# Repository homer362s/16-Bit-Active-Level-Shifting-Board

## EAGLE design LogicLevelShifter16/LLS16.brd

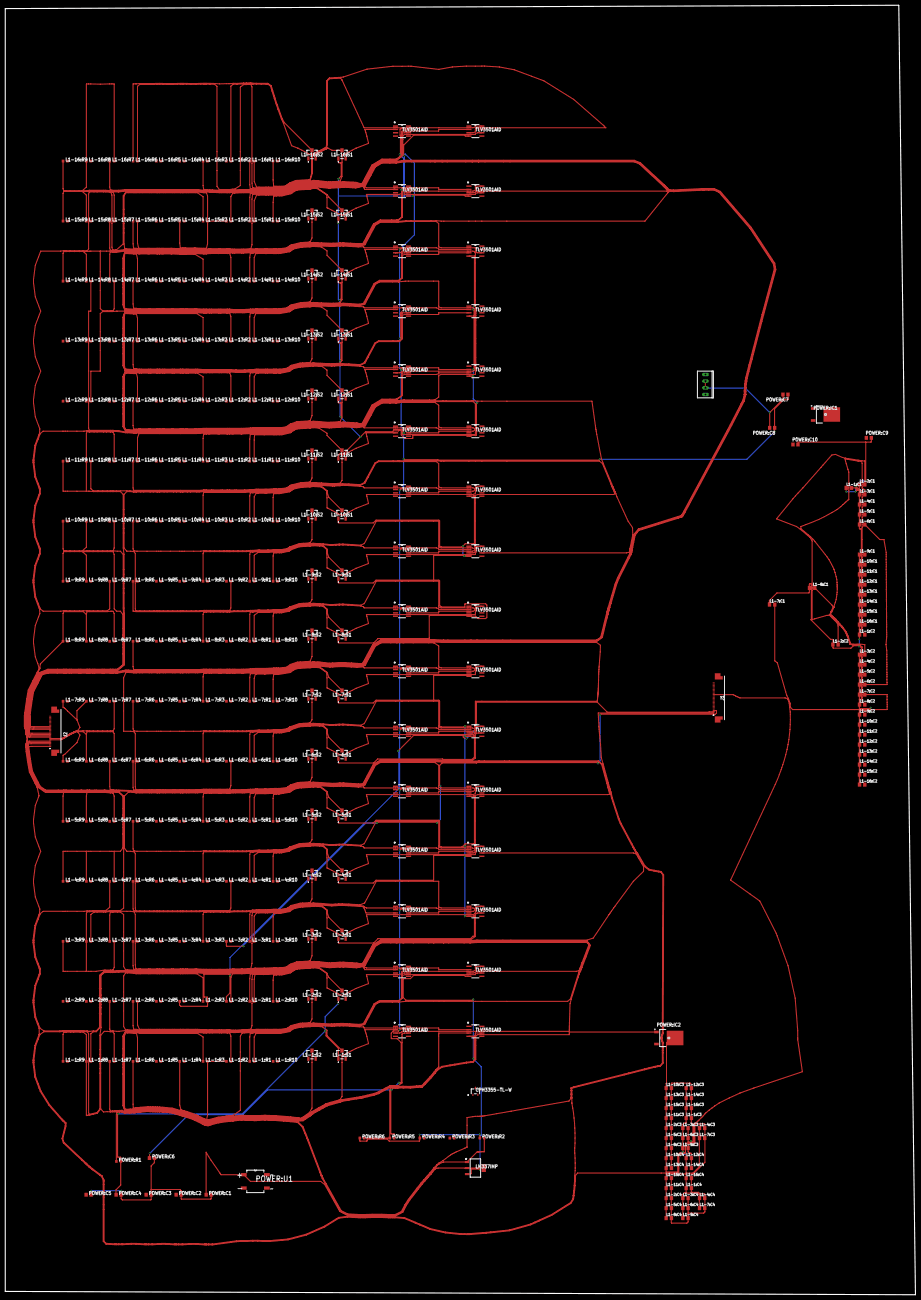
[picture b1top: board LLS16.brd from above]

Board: 2 copper layers, 346.7 x 491.2 mm, 312 parts (0 on the bottom side), 220 nets.

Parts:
J1, J2: 0524372471
L1-1:C1, L1-1:C2, L1-1:C3, L1-1:C4, L1-2:C1, L1-2:C2, L1-2:C3, L1-2:C4, L1-3:C1, L1-3:C2, L1-3:C3, L1-3:C4, L1-4:C1, L1-4:C2, L1-4:C3, L1-4:C4, L1-5:C1, L1-5:C2, L1-5:C3, L1-5:C4, L1-6:C1, L1-6:C2, L1-6:C3, L1-6:C4, L1-7:C1, L1-7:C2, L1-7:C3, L1-7:C4, L1-8:C1, L1-8:C2, L1-8:C3, L1-8:C4, L1-9:C1, L1-9:C2, L1-9:C3, L1-9:C4, L1-10:C1, L1-10:C2, L1-10:C3, L1-10:C4, L1-11:C1, L1-11:C2, L1-11:C3, L1-11:C4, L1-12:C1, L1-12:C2, L1-12:C3, L1-12:C4, L1-13:C1, L1-13:C2, L1-13:C3, L1-13:C4, L1-14:C1, L1-14:C2, L1-14:C3, L1-14:C4, L1-15:C1, L1-15:C2, L1-15:C3, L1-15:C4, L1-16:C1, L1-16:C2, L1-16:C3, L1-16:C4: C0805K
L1-1:R1, L1-1:R2, L1-1:R6, L1-1:R8, L1-2:R1, L1-2:R2, L1-2:R6, L1-2:R8, L1-3:R1, L1-3:R2, L1-3:R6, L1-3:R8, L1-4:R1, L1-4:R2, L1-4:R6, L1-4:R8, L1-5:R1, L1-5:R2, L1-5:R6, L1-5:R8, L1-6:R1, L1-6:R2, L1-6:R6, L1-6:R8, L1-7:R1, L1-7:R2, L1-7:R6, L1-7:R8, L1-8:R1, L1-8:R2, L1-8:R6, L1-8:R8, L1-9:R1, L1-9:R2, L1-9:R6, L1-9:R8, L1-10:R1, L1-10:R2, L1-10:R6, L1-10:R8, L1-11:R1, L1-11:R2, L1-11:R6, L1-11:R8, L1-12:R1, L1-12:R2, L1-12:R6, L1-12:R8, L1-13:R1, L1-13:R2, L1-13:R6, L1-13:R8, L1-14:R1, L1-14:R2, L1-14:R6, L1-14:R8, L1-15:R1, L1-15:R2, L1-15:R6, L1-15:R8, L1-16:R1, L1-16:R2, L1-16:R6, L1-16:R8: 130; R0603
L1-1:R3, L1-1:R4, L1-1:R7, L1-1:R9, L1-1:R10, L1-2:R3, L1-2:R4, L1-2:R7, L1-2:R9, L1-2:R10, L1-3:R3, L1-3:R4, L1-3:R7, L1-3:R9, L1-3:R10, L1-4:R3, L1-4:R4, L1-4:R7, L1-4:R9, L1-4:R10, L1-5:R3, L1-5:R4, L1-5:R7, L1-5:R9, L1-5:R10, L1-6:R3, L1-6:R4, L1-6:R7, L1-6:R9, L1-6:R10, L1-7:R3, L1-7:R4, L1-7:R7, L1-7:R9, L1-7:R10, L1-8:R3, L1-8:R4, L1-8:R7, L1-8:R9, L1-8:R10, L1-9:R3, L1-9:R4, L1-9:R7, L1-9:R9, L1-9:R10, L1-10:R3, L1-10:R4, L1-10:R7, L1-10:R9, L1-10:R10, L1-11:R3, L1-11:R4, L1-11:R7, L1-11:R9, L1-11:R10, L1-12:R3, L1-12:R4, L1-12:R7, L1-12:R9, L1-12:R10, L1-13:R3, L1-13:R4, L1-13:R7, L1-13:R9, L1-13:R10, L1-14:R3, L1-14:R4, L1-14:R7, L1-14:R9, L1-14:R10, L1-15:R3, L1-15:R4, L1-15:R7, L1-15:R9, L1-15:R10, L1-16:R3, L1-16:R4, L1-16:R7, L1-16:R9, L1-16:R10: 220; R0603
L1-1:R5, L1-2:R5, L1-3:R5, L1-4:R5, L1-5:R5, L1-6:R5, L1-7:R5, L1-8:R5, L1-9:R5, L1-10:R5, L1-11:R5, L1-12:R5, L1-13:R5, L1-14:R5, L1-15:R5, L1-16:R5: 51; R0603
L1-1:S1, L1-1:S2, L1-2:S1, L1-2:S2, L1-3:S1, L1-3:S2, L1-4:S1, L1-4:S2, L1-5:S1, L1-5:S2, L1-6:S1, L1-6:S2, L1-7:S1, L1-7:S2, L1-8:S1, L1-8:S2, L1-9:S1, L1-9:S2, L1-10:S1, L1-10:S2, L1-11:S1, L1-11:S2, L1-12:S1, L1-12:S2, L1-13:S1, L1-13:S2, L1-14:S1, L1-14:S2, L1-15:S1, L1-15:S2, L1-16:S1, L1-16:S2: SM-3TW102; SM3TW102
L1-1:U1, L1-1:U2, L1-2:U1, L1-2:U2, L1-3:U1, L1-3:U2, L1-4:U1, L1-4:U2, L1-5:U1, L1-5:U2, L1-6:U1, L1-6:U2, L1-7:U1, L1-7:U2, L1-8:U1, L1-8:U2, L1-9:U1, L1-9:U2, L1-10:U1, L1-10:U2, L1-11:U1, L1-11:U2, L1-12:U1, L1-12:U2, L1-13:U1, L1-13:U2, L1-14:U1, L1-14:U2, L1-15:U1, L1-15:U2, L1-16:U1, L1-16:U2: TLV3501AID; D8
POWER:C1, POWER:C2, POWER:C3: 10uF; C0805
POWER:C4, POWER:C5, POWER:C6: 0.1uF; C0805
POWER:C7, POWER:C9: 0.1 uF; C0805
POWER:C8, POWER:C10: 2.2 uF; C0805
POWER:IC1, POWER:IC2: LM317AMDT_NOPB; TO228P991X238-3N
POWER:R1, POWER:R3, POWER:R5: 240; R0603
POWER:R2, POWER:R4, POWER:R6: 49.9; R0603
POWER:U1: DF10S; SOT508P985X260-4N
POWER:U2: LM337IMP; MP04A_TEX
U1: CPH3355-TL-W; CPH3_2P9X1P6_ONS
U$1: CONNHEADERVERT4POS2.54MM

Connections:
+1.5V: L1-1:S1.3, L1-1:S2.1, L1-1:U1.7, L1-2:S1.3, L1-2:S2.1, L1-2:U1.7, L1-3:S1.3, L1-3:S2.1, L1-3:U1.7, L1-4:S1.3, L1-4:S2.1, L1-4:U1.7, L1-5:S1.3, L1-5:S2.1, L1-5:U1.7, L1-6:S1.3, L1-6:S2.1, L1-6:U1.7, L1-7:S1.3, L1-7:S2.1, L1-7:U1.7, L1-8:S1.3, L1-8:S2.1, L1-8:U1.7, L1-9:S1.3, L1-9:S2.1, L1-9:U1.7, L1-10:S1.3, L1-10:S2.1, L1-10:U1.7, L1-11:S1.3, L1-11:S2.1, L1-11:U1.7, L1-12:S1.3, L1-12:S2.1, L1-12:U1.7, L1-13:S1.3, L1-13:S2.1, L1-13:U1.7, L1-14:S1.3, L1-14:S2.1, L1-14:U1.7, L1-15:S1.3, L1-15:S2.1, L1-15:U1.7, L1-16:S1.3, L1-16:S2.1, L1-16:U1.7, POWER:C5.1, POWER:C9.1, POWER:C10.1, POWER:IC1.4, POWER:R3.2, U1.2
+3V: L1-1:C3.1, L1-1:C4.1, L1-1:U2.7, L1-2:C3.1, L1-2:C4.1, L1-2:U2.7, L1-3:C3.1, L1-3:C4.1, L1-3:U2.7, L1-4:C3.1, L1-4:C4.1, L1-4:U2.7, L1-5:C3.1, L1-5:C4.1, L1-5:U2.7, L1-6:C3.1, L1-6:C4.1, L1-6:U2.7, L1-7:C3.1, L1-7:C4.1, L1-7:U2.7, L1-8:C3.1, L1-8:C4.1, L1-8:U2.7, L1-9:C3.1, L1-9:C4.1, L1-9:U2.7, L1-10:C3.1, L1-10:C4.1, L1-10:U2.7, L1-11:C3.1, L1-11:C4.1, L1-11:U2.7, L1-12:C3.1, L1-12:C4.1, L1-12:U2.7, L1-13:C3.1, L1-13:C4.1, L1-13:U2.7, L1-14:C3.1, L1-14:C4.1, L1-14:U2.7, L1-15:C3.1, L1-15:C4.1, L1-15:U2.7, L1-16:C3.1, L1-16:C4.1, L1-16:U2.7, POWER:C6.1, POWER:C7.1, POWER:C8.1, POWER:IC2.4, POWER:R5.2
+5V: POWER:U1.4, U$1.4
-1.5V: L1-1:C1.1, L1-1:C2.1, L1-1:S1.1, L1-1:U1.4, L1-2:C1.1, L1-2:C2.1, L1-2:S1.1, L1-2:U1.4, L1-3:C1.1, L1-3:C2.1, L1-3:S1.1, L1-3:U1.4, L1-4:C1.1, L1-4:C2.1, L1-4:S1.1, L1-4:U1.4, L1-5:C1.1, L1-5:C2.1, L1-5:S1.1, L1-5:U1.4, L1-6:C1.1, L1-6:C2.1, L1-6:S1.1, L1-6:U1.4, L1-7:C1.1, L1-7:C2.1, L1-7:S1.1, L1-7:U1.4, L1-8:C1.1, L1-8:C2.1, L1-8:S1.1, L1-8:U1.4, L1-9:C1.1, L1-9:C2.1, L1-9:S1.1, L1-9:U1.4, L1-10:C1.1, L1-10:C2.1, L1-10:S1.1, L1-10:U1.4, L1-11:C1.1, L1-11:C2.1, L1-11:S1.1, L1-11:U1.4, L1-12:C1.1, L1-12:C2.1, L1-12:S1.1, L1-12:U1.4, L1-13:C1.1, L1-13:C2.1, L1-13:S1.1, L1-13:U1.4, L1-14:C1.1, L1-14:C2.1, L1-14:S1.1, L1-14:U1.4, L1-15:C1.1, L1-15:C2.1, L1-15:S1.1, L1-15:U1.4, L1-16:C1.1, L1-16:C2.1, L1-16:S1.1, L1-16:U1.4, POWER:C4.1, POWER:C9.2, POWER:C10.2, POWER:R1.2, POWER:U2.3
D: L1-1:R5.1, L1-1:U2.8, L1-2:R5.1, L1-2:U2.8, L1-3:R5.1, L1-3:U2.8, L1-4:R5.1, L1-4:U2.8, L1-5:R5.1, L1-5:U2.8, L1-6:R5.1, L1-6:U2.8, L1-7:R5.1, L1-7:U2.8, L1-8:R5.1, L1-8:U2.8, L1-9:R5.1, L1-9:U2.8, L1-10:R5.1, L1-10:U2.8, L1-11:R5.1, L1-11:U2.8, L1-12:R5.1, L1-12:U2.8, L1-13:R5.1, L1-13:U2.8, L1-14:R5.1, L1-14:U2.8, L1-15:R5.1, L1-15:U2.8, L1-16:R5.1, L1-16:U2.8, U1.3
F1: J1.1, L1-1:R2.1, L1-1:R3.2, L1-1:R4.1
F2: J1.2, L1-2:R2.1, L1-2:R3.2, L1-2:R4.1
F3: J1.3, L1-3:R2.1, L1-3:R3.2, L1-3:R4.1
F4: J1.4, L1-4:R2.1, L1-4:R3.2, L1-4:R4.1
F5: J1.5, L1-5:R2.1, L1-5:R3.2, L1-5:R4.1
F6: J1.6, L1-6:R2.1, L1-6:R3.2, L1-6:R4.1
F7: J1.7, L1-7:R2.1, L1-7:R3.2, L1-7:R4.1
F8: J1.8, L1-8:R2.1, L1-8:R3.2, L1-8:R4.1
F9: J1.9, L1-9:R2.1, L1-9:R3.2, L1-9:R4.1
F10: J1.10, L1-10:R2.1, L1-10:R3.2, L1-10:R4.1
F11: J1.11, L1-11:R2.1, L1-11:R3.2, L1-11:R4.1
F12: J1.12, L1-12:R2.1, L1-12:R3.2, L1-12:R4.1
F13: J1.13, L1-13:R2.1, L1-13:R3.2, L1-13:R4.1
F14: J1.14, L1-14:R2.1, L1-14:R3.2, L1-14:R4.1
F15: J1.15, L1-15:R2.1, L1-15:R3.2, L1-15:R4.1
F16: J1.16, L1-16:R2.1, L1-16:R3.2, L1-16:R4.1
G: L1-1:R10.2, L1-2:R10.2, L1-3:R10.2, L1-4:R10.2, L1-5:R10.2, L1-6:R10.2, L1-7:R10.2, L1-8:R10.2, L1-9:R10.2, L1-10:R10.2, L1-11:R10.2, L1-12:R10.2, L1-13:R10.2, L1-14:R10.2, L1-15:R10.2, L1-16:R10.2, U1.1
GND: L1-1:C3.2, L1-1:C4.2, L1-2:C3.2, L1-2:C4.2, L1-3:C3.2, L1-3:C4.2, L1-4:C3.2, L1-4:C4.2, L1-5:C3.2, L1-5:C4.2, L1-6:C3.2, L1-6:C4.2, L1-7:C3.2, L1-7:C4.2, L1-8:C3.2, L1-8:C4.2, L1-9:C3.2, L1-9:C4.2, L1-10:C3.2, L1-10:C4.2, L1-11:C3.2, L1-11:C4.2, L1-12:C3.2, L1-12:C4.2, L1-13:C3.2, L1-13:C4.2, L1-14:C3.2, L1-14:C4.2, L1-15:C3.2, L1-15:C4.2, L1-16:C3.2, L1-16:C4.2, POWER:C1.2, POWER:C2.2, POWER:C3.2, POWER:C4.2, POWER:C5.2, POWER:C6.2, POWER:C7.2, POWER:C8.2, POWER:R2.1, POWER:R4.1, POWER:R6.1, U$1.2, U$1.3
L1-1:+1.5: L1-1:C1.2, L1-1:C2.2
L1-1:GND!: L1-1:R4.2, L1-1:R5.2, L1-1:R9.2, L1-1:S2.3, L1-1:U2.4
L1-1:N$1: L1-1:R1.2, L1-1:S1.2
L1-1:N$2: L1-1:R1.1, L1-1:U1.2
L1-1:N$3: L1-1:R2.2, L1-1:U1.3
L1-1:N$5: L1-1:R3.1, L1-1:U2.6
L1-1:N$6: L1-1:R6.1, L1-1:S2.2
L1-1:N$7: L1-1:R6.2, L1-1:U2.2
L1-1:N$8: L1-1:R8.2, L1-1:U2.3
L1-1:N$10: L1-1:R7.1, L1-1:U1.6
L1-1:N$11: L1-1:R10.1, L1-1:U1.8
L1-2:+1.5: L1-2:C1.2, L1-2:C2.2
L1-2:GND!: L1-2:R4.2, L1-2:R5.2, L1-2:R9.2, L1-2:S2.3, L1-2:U2.4
L1-2:N$1: L1-2:R1.2, L1-2:S1.2
L1-2:N$2: L1-2:R1.1, L1-2:U1.2
L1-2:N$3: L1-2:R2.2, L1-2:U1.3
L1-2:N$5: L1-2:R3.1, L1-2:U2.6
L1-2:N$6: L1-2:R6.1, L1-2:S2.2
L1-2:N$7: L1-2:R6.2, L1-2:U2.2
L1-2:N$8: L1-2:R8.2, L1-2:U2.3
L1-2:N$10: L1-2:R7.1, L1-2:U1.6
L1-2:N$11: L1-2:R10.1, L1-2:U1.8
L1-3:+1.5: L1-3:C1.2, L1-3:C2.2
L1-3:GND!: L1-3:R4.2, L1-3:R5.2, L1-3:R9.2, L1-3:S2.3, L1-3:U2.4
L1-3:N$1: L1-3:R1.2, L1-3:S1.2
L1-3:N$2: L1-3:R1.1, L1-3:U1.2
L1-3:N$3: L1-3:R2.2, L1-3:U1.3
L1-3:N$5: L1-3:R3.1, L1-3:U2.6
L1-3:N$6: L1-3:R6.1, L1-3:S2.2
L1-3:N$7: L1-3:R6.2, L1-3:U2.2
L1-3:N$8: L1-3:R8.2, L1-3:U2.3
L1-3:N$10: L1-3:R7.1, L1-3:U1.6
L1-3:N$11: L1-3:R10.1, L1-3:U1.8
L1-4:+1.5: L1-4:C1.2, L1-4:C2.2
L1-4:GND!: L1-4:R4.2, L1-4:R5.2, L1-4:R9.2, L1-4:S2.3, L1-4:U2.4
L1-4:N$1: L1-4:R1.2, L1-4:S1.2
L1-4:N$2: L1-4:R1.1, L1-4:U1.2
L1-4:N$3: L1-4:R2.2, L1-4:U1.3
L1-4:N$5: L1-4:R3.1, L1-4:U2.6
L1-4:N$6: L1-4:R6.1, L1-4:S2.2
L1-4:N$7: L1-4:R6.2, L1-4:U2.2
L1-4:N$8: L1-4:R8.2, L1-4:U2.3
L1-4:N$10: L1-4:R7.1, L1-4:U1.6
L1-4:N$11: L1-4:R10.1, L1-4:U1.8
L1-5:+1.5: L1-5:C1.2, L1-5:C2.2
L1-5:GND!: L1-5:R4.2, L1-5:R5.2, L1-5:R9.2, L1-5:S2.3, L1-5:U2.4
L1-5:N$1: L1-5:R1.2, L1-5:S1.2
L1-5:N$2: L1-5:R1.1, L1-5:U1.2
L1-5:N$3: L1-5:R2.2, L1-5:U1.3
L1-5:N$5: L1-5:R3.1, L1-5:U2.6
L1-5:N$6: L1-5:R6.1, L1-5:S2.2
L1-5:N$7: L1-5:R6.2, L1-5:U2.2
L1-5:N$8: L1-5:R8.2, L1-5:U2.3
L1-5:N$10: L1-5:R7.1, L1-5:U1.6
L1-5:N$11: L1-5:R10.1, L1-5:U1.8
L1-6:+1.5: L1-6:C1.2, L1-6:C2.2
L1-6:GND!: L1-6:R4.2, L1-6:R5.2, L1-6:R9.2, L1-6:S2.3, L1-6:U2.4
L1-6:N$1: L1-6:R1.2, L1-6:S1.2
L1-6:N$2: L1-6:R1.1, L1-6:U1.2
L1-6:N$3: L1-6:R2.2, L1-6:U1.3
L1-6:N$5: L1-6:R3.1, L1-6:U2.6
L1-6:N$6: L1-6:R6.1, L1-6:S2.2
L1-6:N$7: L1-6:R6.2, L1-6:U2.2
L1-6:N$8: L1-6:R8.2, L1-6:U2.3
L1-6:N$10: L1-6:R7.1, L1-6:U1.6
L1-6:N$11: L1-6:R10.1, L1-6:U1.8
L1-7:+1.5: L1-7:C1.2, L1-7:C2.2
L1-7:GND!: L1-7:R4.2, L1-7:R5.2, L1-7:R9.2, L1-7:S2.3, L1-7:U2.4
L1-7:N$1: L1-7:R1.2, L1-7:S1.2
L1-7:N$2: L1-7:R1.1, L1-7:U1.2
L1-7:N$3: L1-7:R2.2, L1-7:U1.3
L1-7:N$5: L1-7:R3.1, L1-7:U2.6
L1-7:N$6: L1-7:R6.1, L1-7:S2.2
L1-7:N$7: L1-7:R6.2, L1-7:U2.2
L1-7:N$8: L1-7:R8.2, L1-7:U2.3
L1-7:N$10: L1-7:R7.1, L1-7:U1.6
L1-7:N$11: L1-7:R10.1, L1-7:U1.8
L1-8:+1.5: L1-8:C1.2, L1-8:C2.2
L1-8:GND!: L1-8:R4.2, L1-8:R5.2, L1-8:R9.2, L1-8:S2.3, L1-8:U2.4
L1-8:N$1: L1-8:R1.2, L1-8:S1.2
L1-8:N$2: L1-8:R1.1, L1-8:U1.2
L1-8:N$3: L1-8:R2.2, L1-8:U1.3
L1-8:N$5: L1-8:R3.1, L1-8:U2.6
L1-8:N$6: L1-8:R6.1, L1-8:S2.2
L1-8:N$7: L1-8:R6.2, L1-8:U2.2
L1-8:N$8: L1-8:R8.2, L1-8:U2.3
L1-8:N$10: L1-8:R7.1, L1-8:U1.6
L1-8:N$11: L1-8:R10.1, L1-8:U1.8
L1-9:+1.5: L1-9:C1.2, L1-9:C2.2
L1-9:GND!: L1-9:R4.2, L1-9:R5.2, L1-9:R9.2, L1-9:S2.3, L1-9:U2.4
L1-9:N$1: L1-9:R1.2, L1-9:S1.2
L1-9:N$2: L1-9:R1.1, L1-9:U1.2
L1-9:N$3: L1-9:R2.2, L1-9:U1.3
L1-9:N$5: L1-9:R3.1, L1-9:U2.6
L1-9:N$6: L1-9:R6.1, L1-9:S2.2
L1-9:N$7: L1-9:R6.2, L1-9:U2.2
L1-9:N$8: L1-9:R8.2, L1-9:U2.3
L1-9:N$10: L1-9:R7.1, L1-9:U1.6
L1-9:N$11: L1-9:R10.1, L1-9:U1.8
L1-10:+1.5: L1-10:C1.2, L1-10:C2.2
L1-10:GND!: L1-10:R4.2, L1-10:R5.2, L1-10:R9.2, L1-10:S2.3, L1-10:U2.4
L1-10:N$1: L1-10:R1.2, L1-10:S1.2
L1-10:N$2: L1-10:R1.1, L1-10:U1.2
L1-10:N$3: L1-10:R2.2, L1-10:U1.3
L1-10:N$5: L1-10:R3.1, L1-10:U2.6
L1-10:N$6: L1-10:R6.1, L1-10:S2.2
L1-10:N$7: L1-10:R6.2, L1-10:U2.2
L1-10:N$8: L1-10:R8.2, L1-10:U2.3
L1-10:N$10: L1-10:R7.1, L1-10:U1.6
L1-10:N$11: L1-10:R10.1, L1-10:U1.8
L1-11:+1.5: L1-11:C1.2, L1-11:C2.2
L1-11:GND!: L1-11:R4.2, L1-11:R5.2, L1-11:R9.2, L1-11:S2.3, L1-11:U2.4
L1-11:N$1: L1-11:R1.2, L1-11:S1.2
L1-11:N$2: L1-11:R1.1, L1-11:U1.2
L1-11:N$3: L1-11:R2.2, L1-11:U1.3
L1-11:N$5: L1-11:R3.1, L1-11:U2.6
L1-11:N$6: L1-11:R6.1, L1-11:S2.2
L1-11:N$7: L1-11:R6.2, L1-11:U2.2
L1-11:N$8: L1-11:R8.2, L1-11:U2.3
L1-11:N$10: L1-11:R7.1, L1-11:U1.6
L1-11:N$11: L1-11:R10.1, L1-11:U1.8
L1-12:+1.5: L1-12:C1.2, L1-12:C2.2
L1-12:GND!: L1-12:R4.2, L1-12:R5.2, L1-12:R9.2, L1-12:S2.3, L1-12:U2.4
L1-12:N$1: L1-12:R1.2, L1-12:S1.2
L1-12:N$2: L1-12:R1.1, L1-12:U1.2
L1-12:N$3: L1-12:R2.2, L1-12:U1.3
L1-12:N$5: L1-12:R3.1, L1-12:U2.6
L1-12:N$6: L1-12:R6.1, L1-12:S2.2
L1-12:N$7: L1-12:R6.2, L1-12:U2.2
L1-12:N$8: L1-12:R8.2, L1-12:U2.3
L1-12:N$10: L1-12:R7.1, L1-12:U1.6
L1-12:N$11: L1-12:R10.1, L1-12:U1.8
L1-13:+1.5: L1-13:C1.2, L1-13:C2.2
L1-13:GND!: L1-13:R4.2, L1-13:R5.2, L1-13:R9.2, L1-13:S2.3, L1-13:U2.4
L1-13:N$1: L1-13:R1.2, L1-13:S1.2
L1-13:N$2: L1-13:R1.1, L1-13:U1.2
L1-13:N$3: L1-13:R2.2, L1-13:U1.3
L1-13:N$5: L1-13:R3.1, L1-13:U2.6
L1-13:N$6: L1-13:R6.1, L1-13:S2.2
L1-13:N$7: L1-13:R6.2, L1-13:U2.2
L1-13:N$8: L1-13:R8.2, L1-13:U2.3
L1-13:N$10: L1-13:R7.1, L1-13:U1.6
L1-13:N$11: L1-13:R10.1, L1-13:U1.8
L1-14:+1.5: L1-14:C1.2, L1-14:C2.2
L1-14:GND!: L1-14:R4.2, L1-14:R5.2, L1-14:R9.2, L1-14:S2.3, L1-14:U2.4
L1-14:N$1: L1-14:R1.2, L1-14:S1.2
L1-14:N$2: L1-14:R1.1, L1-14:U1.2
L1-14:N$3: L1-14:R2.2, L1-14:U1.3
L1-14:N$5: L1-14:R3.1, L1-14:U2.6
L1-14:N$6: L1-14:R6.1, L1-14:S2.2
L1-14:N$7: L1-14:R6.2, L1-14:U2.2
L1-14:N$8: L1-14:R8.2, L1-14:U2.3
L1-14:N$10: L1-14:R7.1, L1-14:U1.6
L1-14:N$11: L1-14:R10.1, L1-14:U1.8
L1-15:+1.5: L1-15:C1.2, L1-15:C2.2
L1-15:GND!: L1-15:R4.2, L1-15:R5.2, L1-15:R9.2, L1-15:S2.3, L1-15:U2.4
L1-15:N$1: L1-15:R1.2, L1-15:S1.2
L1-15:N$2: L1-15:R1.1, L1-15:U1.2
L1-15:N$3: L1-15:R2.2, L1-15:U1.3
L1-15:N$5: L1-15:R3.1, L1-15:U2.6
L1-15:N$6: L1-15:R6.1, L1-15:S2.2
L1-15:N$7: L1-15:R6.2, L1-15:U2.2
L1-15:N$8: L1-15:R8.2, L1-15:U2.3
L1-15:N$10: L1-15:R7.1, L1-15:U1.6
L1-15:N$11: L1-15:R10.1, L1-15:U1.8
L1-16:+1.5: L1-16:C1.2, L1-16:C2.2
L1-16:GND!: L1-16:R4.2, L1-16:R5.2, L1-16:R9.2, L1-16:S2.3, L1-16:U2.4
L1-16:N$1: L1-16:R1.2, L1-16:S1.2
L1-16:N$2: L1-16:R1.1, L1-16:U1.2
L1-16:N$3: L1-16:R2.2, L1-16:U1.3
L1-16:N$5: L1-16:R3.1, L1-16:U2.6
L1-16:N$6: L1-16:R6.1, L1-16:S2.2
L1-16:N$7: L1-16:R6.2, L1-16:U2.2
L1-16:N$8: L1-16:R8.2, L1-16:U2.3
L1-16:N$10: L1-16:R7.1, L1-16:U1.6
L1-16:N$11: L1-16:R10.1, L1-16:U1.8
M1: J2.1, L1-1:R7.2, L1-1:R8.1, L1-1:R9.1
M2: J2.2, L1-2:R7.2, L1-2:R8.1, L1-2:R9.1
M3: J2.3, L1-3:R7.2, L1-3:R8.1, L1-3:R9.1
M4: J2.4, L1-4:R7.2, L1-4:R8.1, L1-4:R9.1
M5: J2.5, L1-5:R7.2, L1-5:R8.1, L1-5:R9.1
M6: J2.6, L1-6:R7.2, L1-6:R8.1, L1-6:R9.1
M7: J2.7, L1-7:R7.2, L1-7:R8.1, L1-7:R9.1
M8: J2.8, L1-8:R7.2, L1-8:R8.1, L1-8:R9.1
M9: J2.9, L1-9:R7.2, L1-9:R8.1, L1-9:R9.1
M10: J2.10, L1-10:R7.2, L1-10:R8.1, L1-10:R9.1
M11: J2.11, L1-11:R7.2, L1-11:R8.1, L1-11:R9.1
M12: J2.12, L1-12:R7.2, L1-12:R8.1, L1-12:R9.1
M13: J2.13, L1-13:R7.2, L1-13:R8.1, L1-13:R9.1
M14: J2.14, L1-14:R7.2, L1-14:R8.1, L1-14:R9.1
M15: J2.15, L1-15:R7.2, L1-15:R8.1, L1-15:R9.1
M16: J2.16, L1-16:R7.2, L1-16:R8.1, L1-16:R9.1
POWER:N$1: POWER:C1.1, POWER:U1.1, POWER:U2.2, POWER:U2.4
POWER:N$2: POWER:C2.1, POWER:C3.1, POWER:IC1.3, POWER:IC2.3, POWER:U1.2
POWER:N$3: POWER:IC2.1, POWER:R5.1, POWER:R6.2
POWER:N$5: POWER:IC1.1, POWER:R3.1, POWER:R4.2
POWER:N$10: POWER:R1.1, POWER:R2.2, POWER:U2.1

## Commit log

2023-02-16 added bypass Cs
2023-02-23 "Added Capacitors"
2023-02-23 "Prepare to Pull"

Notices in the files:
parts and their libraries:
COPYRIGHT: Copyright (C) 2022 Ultra Librarian. All rights reserved.
COPYRIGHT: Copyright (C) 2023 Ultra Librarian. All rights reserved.
